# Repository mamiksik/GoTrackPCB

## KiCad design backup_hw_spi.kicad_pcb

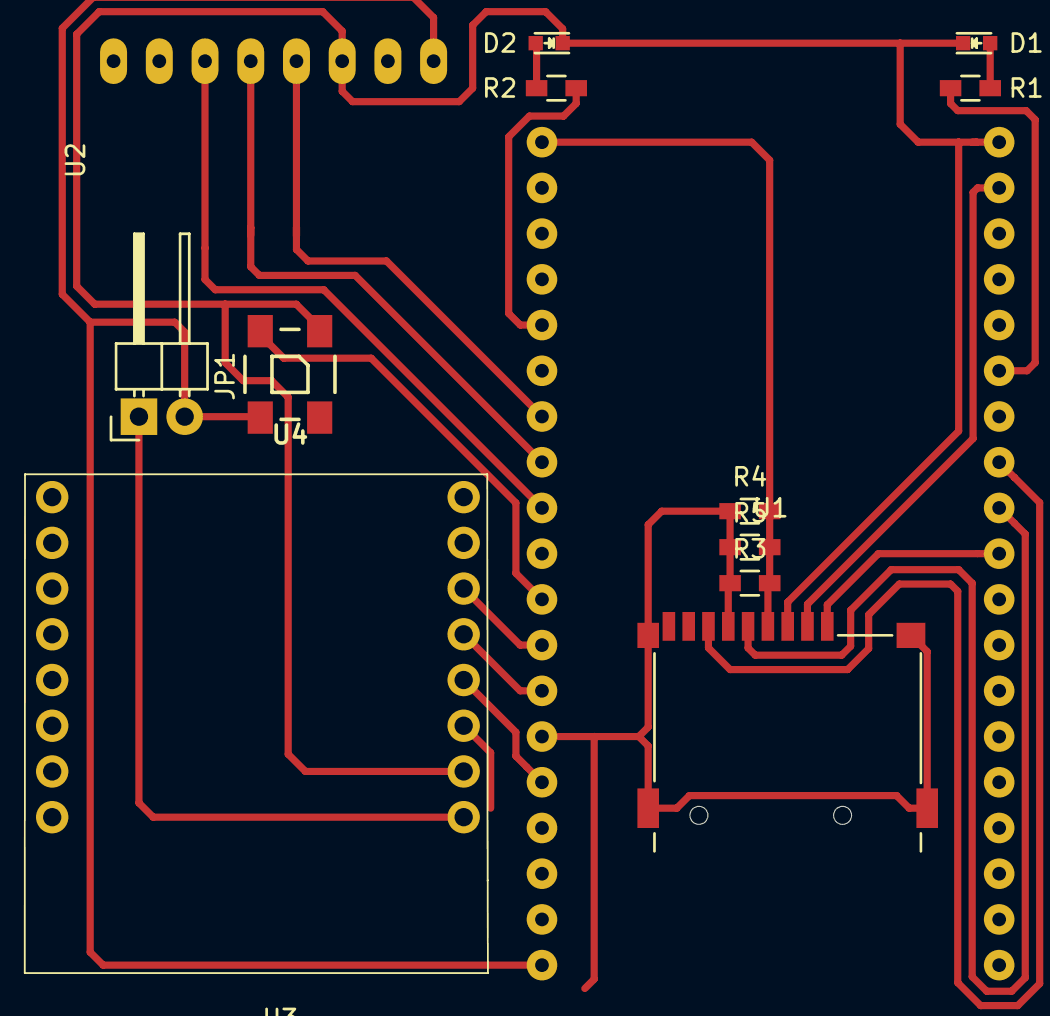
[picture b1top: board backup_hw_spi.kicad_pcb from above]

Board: 2 copper layers, 13 parts (0 on the bottom side), 20 nets.

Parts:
D1, D2: LED; LED_0603
J1: Micro_SD_Card; Conn_uSDcard
JP1: Jumper; Pin_Header_Angled_1x02
R1, R2, R3, R4, R5: R_Small; R_0603_HandSoldering
U1: ESP32-DEVKIT-C
U2: GY-91
U3: Battery_shield_D1_Mini; Battery_shield_D1_mini_board
U4: WS2812B

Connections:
5V: JP1.2, U1.19, U2.1, U4.1
COMMUNICATION_LED: R1.1, U1.36
CS: J1.1, U1.31
GND: D1.1, D2.1, J1.3, J1.6, R3.1, R4.1, R5.1, U1.14, U1.38, U2.3, U3.2, U4.3
MISO: J1.7, U1.28
MOSI: J1.2, U1.30
unnamed: D1.2, R1.2
unnamed: D2.2, R2.2
unnamed: JP1.1, U3.1
POWER_LED: R2.1, U1.5
SCL: U1.6, U2.4
SCLK: J1.5, U1.29
SDA: U1.7, U2.5
SDO: U1.8, U2.6
SMART_LED_IN: U1.11, U4.4
TCK: U1.15, U3.4
TDI: U1.13, U3.5
TDO: U1.23, U3.3
TMS: U1.12, U3.6
VCC: J1.4, R3.2, R4.2, R5.2, U1.1

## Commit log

2017-10-29 And so it begins
